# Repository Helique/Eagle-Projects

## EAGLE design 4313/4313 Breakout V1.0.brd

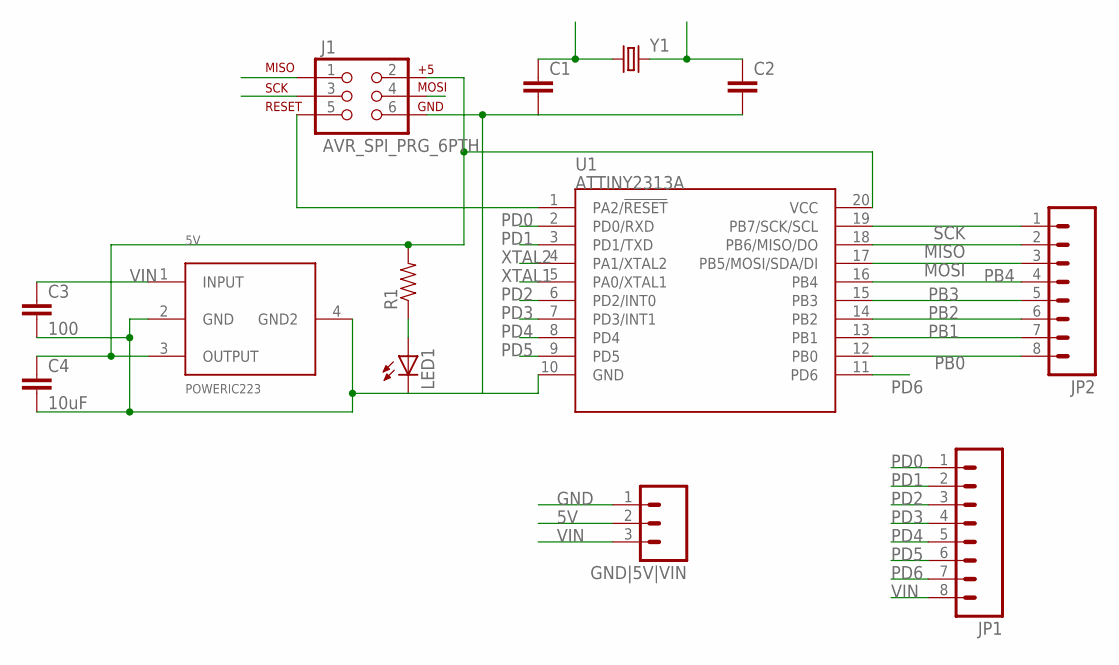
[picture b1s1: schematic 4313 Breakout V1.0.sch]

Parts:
5V: POWERIC223; SOT223
C1, C2: CAP1206; 1206
C3: 100; 1210
C4: 10uF; 1210
GND|5V|VIN: M03PTH; 1X03
J1: AVR_SPI_PRG_6PTH; 2X3
JP1, JP2: M081X08; 1X08
LED1: LED1206; LED-1206
R1: RESISTOR1206; 1206
U1: ATTINY2313A; SOP20W
Y1: CRYSTALHC49US; HC49US

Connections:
5V: 5V.3 (OUTPUT), C4.1, GND|5V|VIN.2, J1.2, R1.2, U1.20 (VCC)
GND: 5V.2 (GND), 5V.4 (GND2), C1.2, C2.2, C3.2, C4.2, GND|5V|VIN.1, J1.6, LED1.C, U1.10 (GND)
MISO: J1.1, JP2.2, U1.18 (PB6/MISO/DO)
MOSI: J1.4, JP2.3, U1.17 (PB5/MOSI/SDA/DI)
unnamed: LED1.A, R1.1
unnamed: J1.5, U1.1 (PA2/!RESET)
PB0: JP2.8, U1.12 (PB0)
PB1: JP2.7, U1.13 (PB1)
PB2: JP2.6, U1.14 (PB2)
PB3: JP2.5, U1.15 (PB3)
PB4: JP2.4, U1.16 (PB4)
PD0: JP1.1, U1.2 (PD0/RXD)
PD1: JP1.2, U1.3 (PD1/TXD)
PD2: JP1.3, U1.6 (PD2/INT0)
PD3: JP1.4, U1.7 (PD3/INT1)
PD4: JP1.5, U1.8 (PD4)
PD5: JP1.6, U1.9 (PD5)
PD6: JP1.7, U1.11 (PD6)
SCK: J1.3, JP2.1, U1.19 (PB7/SCK/SCL)
VIN: 5V.1 (INPUT), C3.1, GND|5V|VIN.3, JP1.8
XTAL1: C1.1, U1.5 (PA0/XTAL1), Y1.1
XTAL2: C2.1, U1.4 (PA1/XTAL2), Y1.2

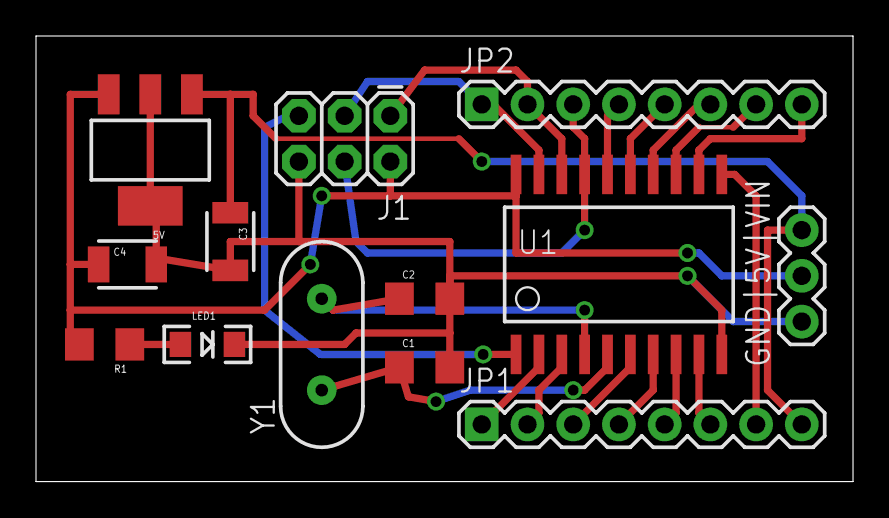
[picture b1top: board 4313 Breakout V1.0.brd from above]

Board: 2 copper layers, 45.4 x 24.8 mm, 13 parts (0 on the bottom side), 22 nets.

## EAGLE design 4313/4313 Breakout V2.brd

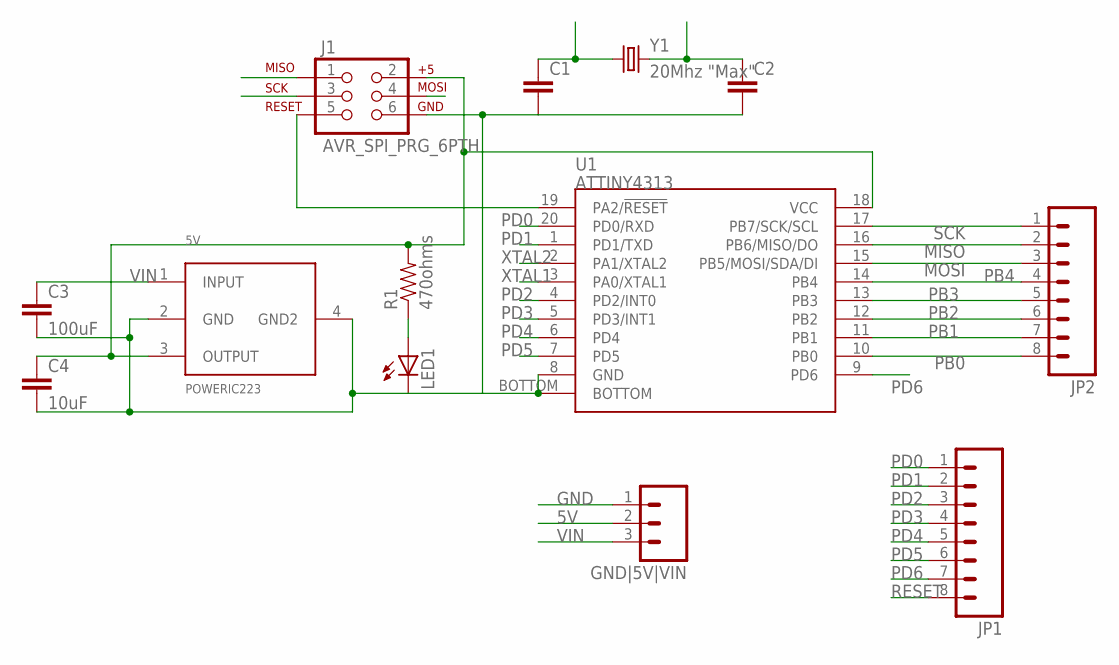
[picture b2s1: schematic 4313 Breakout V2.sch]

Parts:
5V: POWERIC223; SOT223
C1, C2: CAP1206; 1206
C3: 100uF; 1210
C4: 10uF; 1210
GND|5V|VIN: M03PTH; 1X03
J1: AVR_SPI_PRG_6PTH; 2X3
JP1, JP2: M081X08; 1X08
LED1: LED1206; LED-1206
R1: 470ohms; 1206
U1: ATTINY4313; MLF-20
Y1: 20Mhz "Max"; CRYSTAL-SMD-5X3

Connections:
5V: 5V.3 (OUTPUT), C4.1, GND|5V|VIN.2, J1.2, R1.2, U1.18 (VCC)
GND: 5V.2 (GND), 5V.4 (GND2), C1.2, C2.2, C3.2, C4.2, GND|5V|VIN.1, J1.6, LED1.C, U1.8 (GND), U1.BOTTOM
MISO: J1.1, JP2.2, U1.16 (PB6/MISO/DO)
MOSI: J1.4, JP2.3, U1.15 (PB5/MOSI/SDA/DI)
unnamed: LED1.A, R1.1
PB0: JP2.8, U1.10 (PB0)
PB1: JP2.7, U1.11 (PB1)
PB2: JP2.6, U1.12 (PB2)
PB3: JP2.5, U1.13 (PB3)
PB4: JP2.4, U1.14 (PB4)
PD0: JP1.1, U1.20 (PD0/RXD)
PD1: JP1.2, U1.1 (PD1/TXD)
PD2: JP1.3, U1.4 (PD2/INT0)
PD3: JP1.4, U1.5 (PD3/INT1)
PD4: JP1.5, U1.6 (PD4)
PD5: JP1.6, U1.7 (PD5)
PD6: JP1.7, U1.9 (PD6)
RESET: J1.5, JP1.8, U1.19 (PA2/!RESET)
SCK: J1.3, JP2.1, U1.17 (PB7/SCK/SCL)
VIN: 5V.1 (INPUT), C3.1, GND|5V|VIN.3
XTAL1: C1.1, U1.3 (PA0/XTAL1), Y1.1
XTAL2: C2.1, U1.2 (PA1/XTAL2), Y1.3 (2)

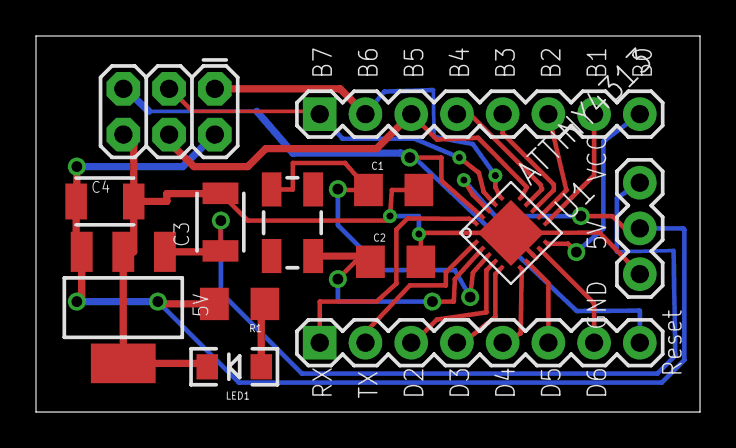
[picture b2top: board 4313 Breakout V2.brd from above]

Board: 2 copper layers, 36.9 x 20.9 mm, 13 parts (0 on the bottom side), 22 nets.

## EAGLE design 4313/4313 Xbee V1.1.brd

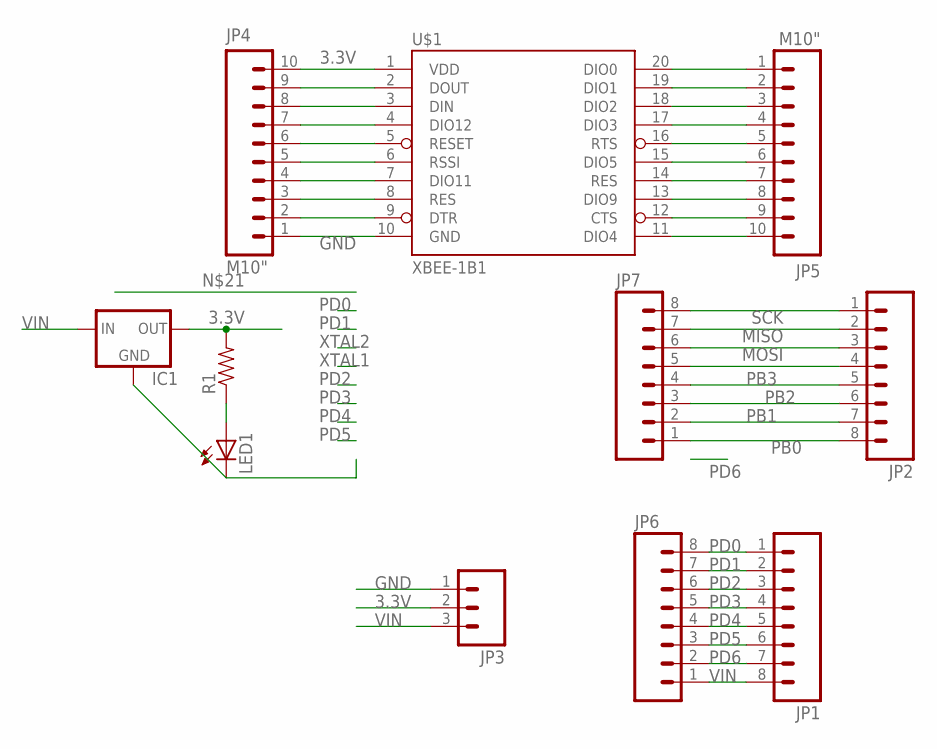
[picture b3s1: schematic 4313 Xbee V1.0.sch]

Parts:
IC1: V_REG_78XXSIDE; 78XXL
JP1, JP2, JP6, JP7: M081X08; 1X08
JP3: M03PTH; 1X03
JP4, JP5: M10"; 1X10
LED1: LED1206; LED-1206
R1: RESISTOR1206; 1206
U$1: XBEE-1B1; XBEE-1

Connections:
3.3V: IC1.OUT, JP3.2, JP4.10, R1.2, U$1.1 (VDD)
GND: IC1.GND, JP3.1, JP4.1, LED1.C, U$1.10 (GND)
MISO: JP2.2, JP7.7
MOSI: JP2.3, JP7.6
unnamed: LED1.A, R1.1
unnamed: JP4.2, U$1.9 (DTR)
unnamed: JP4.3, U$1.8 (RES)
unnamed: JP4.4, U$1.7 (DIO11)
unnamed: JP4.5, U$1.6 (RSSI)
unnamed: JP4.6, U$1.5 (RESET)
unnamed: JP4.7, U$1.4 (DIO12)
unnamed: JP4.8, U$1.3 (DIN)
unnamed: JP4.9, U$1.2 (DOUT)
unnamed: JP5.1, U$1.20 (DIO0)
unnamed: JP5.2, U$1.19 (DIO1)
unnamed: JP5.3, U$1.18 (DIO2)
unnamed: JP5.4, U$1.17 (DIO3)
unnamed: JP5.5, U$1.16 (RTS)
unnamed: JP5.6, U$1.15 (DIO5)
unnamed: JP5.7, U$1.14 (RES)
unnamed: JP5.8, U$1.13 (DIO9)
unnamed: JP5.9, U$1.12 (CTS)
unnamed: JP5.10, U$1.11 (DIO4)
PB0: JP2.8, JP7.1
PB1: JP2.7, JP7.2
PB2: JP2.6, JP7.3
PB3: JP2.5, JP7.4
PB4: JP2.4, JP7.5
PD0: JP1.1, JP6.8
PD1: JP1.2, JP6.7
PD2: JP1.3, JP6.6
PD3: JP1.4, JP6.5
PD4: JP1.5, JP6.4
PD5: JP1.6, JP6.3
PD6: JP1.7, JP6.2
SCK: JP2.1, JP7.8
VIN: IC1.IN, JP1.8, JP3.3, JP6.1

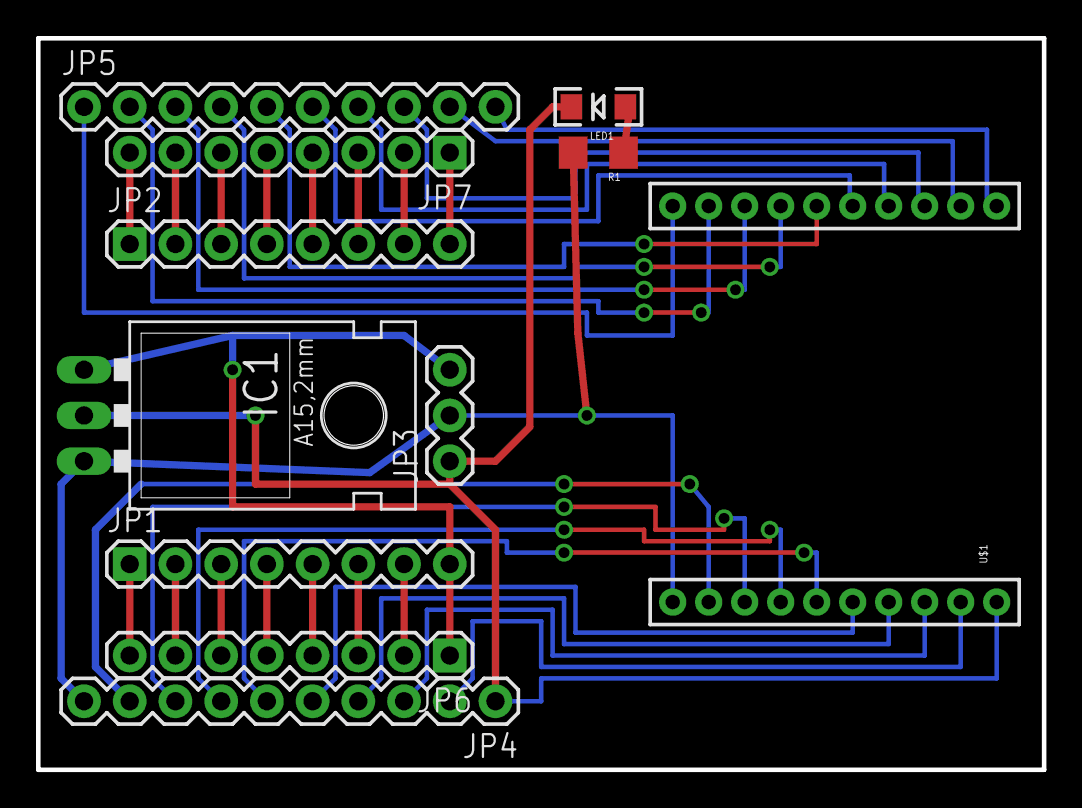
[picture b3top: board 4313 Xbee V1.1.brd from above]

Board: 2 copper layers, 55.9 x 40.6 mm, 11 parts (0 on the bottom side), 37 nets.

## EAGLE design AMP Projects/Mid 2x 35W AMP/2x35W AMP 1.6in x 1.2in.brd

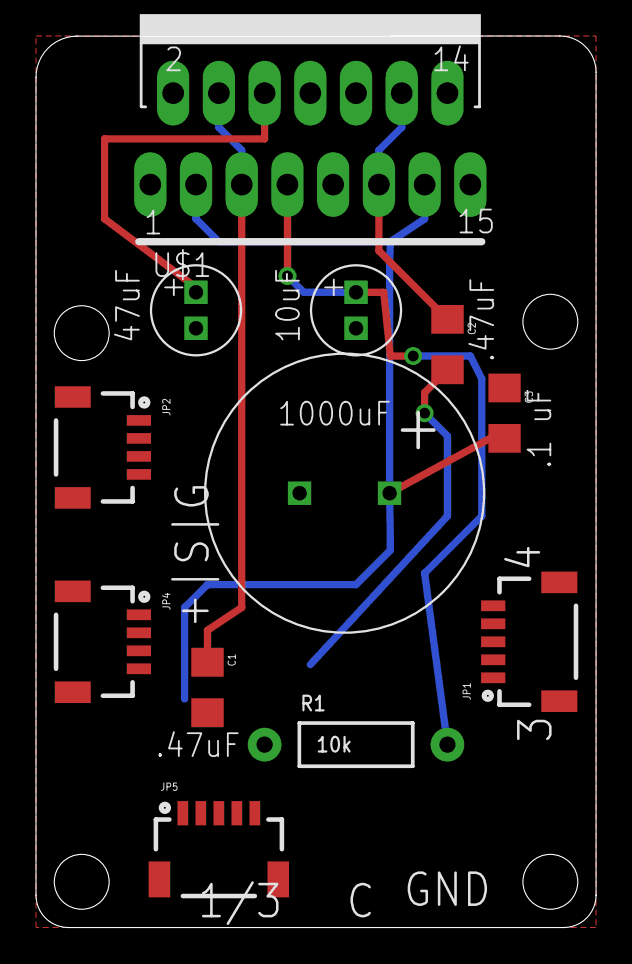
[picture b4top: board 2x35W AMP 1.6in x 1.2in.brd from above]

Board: 2 copper layers, 31.1 x 49.5 mm, 16 parts (0 on the bottom side), 15 nets.

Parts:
10UF, 47UF: 5MM-12.5MM-POLAR2MMX5MM; 2MMLEAD_5MMDIAMETER
1000UF: 5MM-12.5MM-POLAR5MMX12.5MM; 5MMLEAD_12.5MMDIAMETER
C1, C2: .47uF; 1206
C3: .1uF; 1206
JP1, JP5: 1X05-1MM-RA
JP2, JP4: 1X04-1MM-RA
R1: 10k; AXIAL-0.4
U$1: TDA7375V; MULTIWATT-15
U$2, U$3, U$4, U$5: STAND-OFF-TIGHT

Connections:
+5V: JP1.2, JP4.4, JP5.2
CLIP: JP1.5, U$1.10
GND: 10UF.-, 47UF.-, 1000UF.-, C3.1, JP1.1, JP4.1, JP4.3, JP5.1, U$1.8, U$1.9
IN1: C1.1, U$1.4, U$1.5
IN3: C2.1, U$1.11, U$1.12
unnamed: 10UF.+, R1.P$2, U$1.7
unnamed: 47UF.+, U$1.6
OUT1: JP2.4, U$1.1
OUT2: JP2.3, U$1.2
OUT3: JP2.2, U$1.15
OUT4: JP2.1, U$1.14
RAW_IN1: C1.2, JP1.4, JP5.4
RAW_IN3: C2.2, JP1.3, JP5.3
ST-BY: JP5.5, R1.P$1
VCC: 1000UF.+, C3.2, JP4.2, U$1.3, U$1.13

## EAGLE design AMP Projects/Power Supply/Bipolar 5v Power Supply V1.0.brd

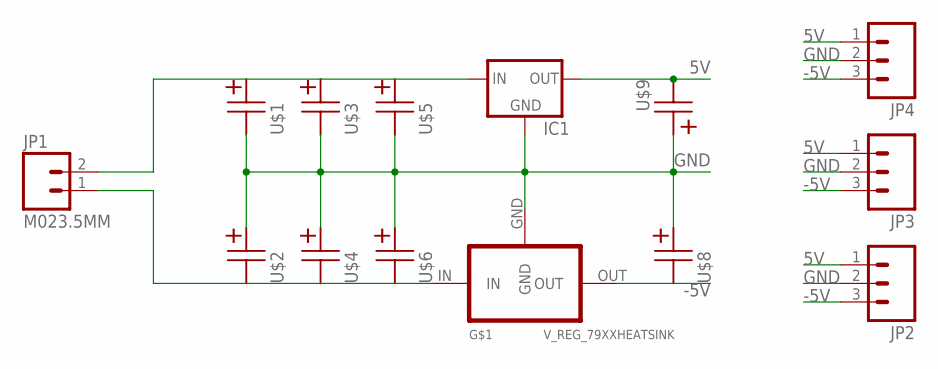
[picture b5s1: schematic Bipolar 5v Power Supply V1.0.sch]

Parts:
IC1: V_REG_78XXSINK; TO220-IGO
JP1: M023.5MM; SCREWTERMINAL-3.5MM-2
JP2, JP3, JP4: M03SCREW; SCREWTERMINAL-3.5MM-3
U$1, U$2, U$3, U$4, U$5, U$6: 5MM-12.5MM-POLAR5MMX12.5MM; 5MMLEAD_12.5MMDIAMETER
U$7: V_REG_79XXHEATSINK; TO220-IGO
U$8, U$9: 5MM-12.5MM-POLAR2MMX5MM; 2MMLEAD_5MMDIAMETER

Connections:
5V: IC1.OUT, JP2.1, JP3.1, JP4.1, U$9.+ (-)
-5V: JP2.3, JP3.3, JP4.3, U$7.OUT, U$8.+ (-)
GND: IC1.GND, JP2.2, JP3.2, JP4.2, U$1.+ (-), U$2.- (+), U$3.+ (-), U$4.- (+), U$5.+ (-), U$6.- (+), U$7.GND, U$8.- (+), U$9.- (+)
RAW+: IC1.IN, JP1.2, U$1.- (+), U$3.- (+), U$5.- (+)
RAW-: JP1.1, U$2.+ (-), U$4.+ (-), U$6.+ (-), U$7.IN

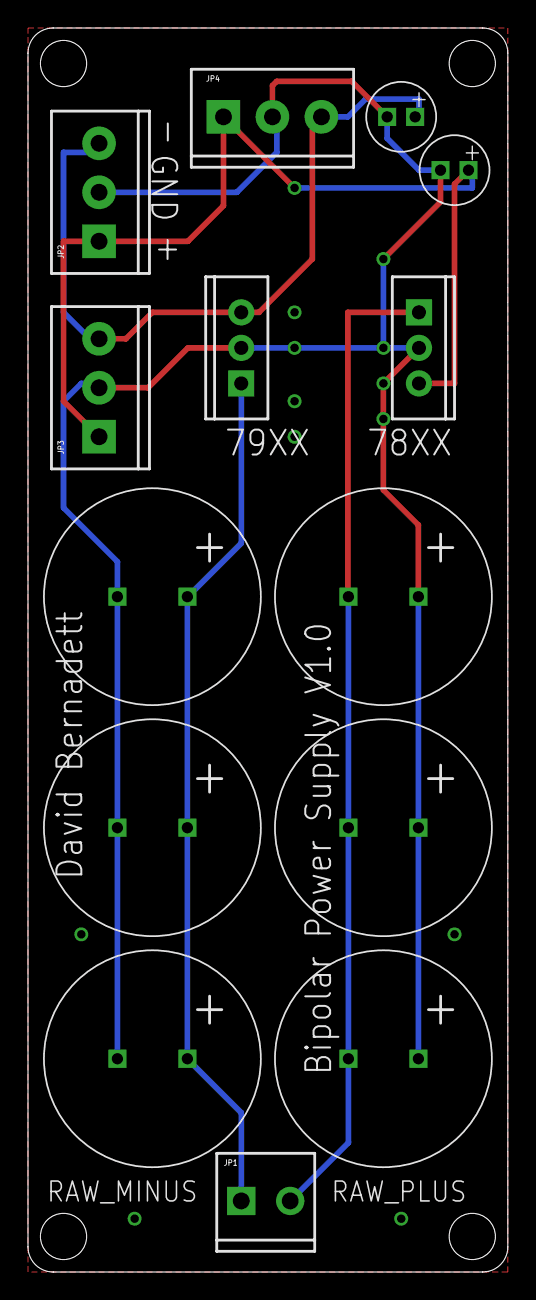
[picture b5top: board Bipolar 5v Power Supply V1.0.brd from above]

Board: 2 copper layers, 34.3 x 88.9 mm, 18 parts (0 on the bottom side), 5 nets.

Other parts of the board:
U$10, U$11, U$12, U$13: STAND-OFF

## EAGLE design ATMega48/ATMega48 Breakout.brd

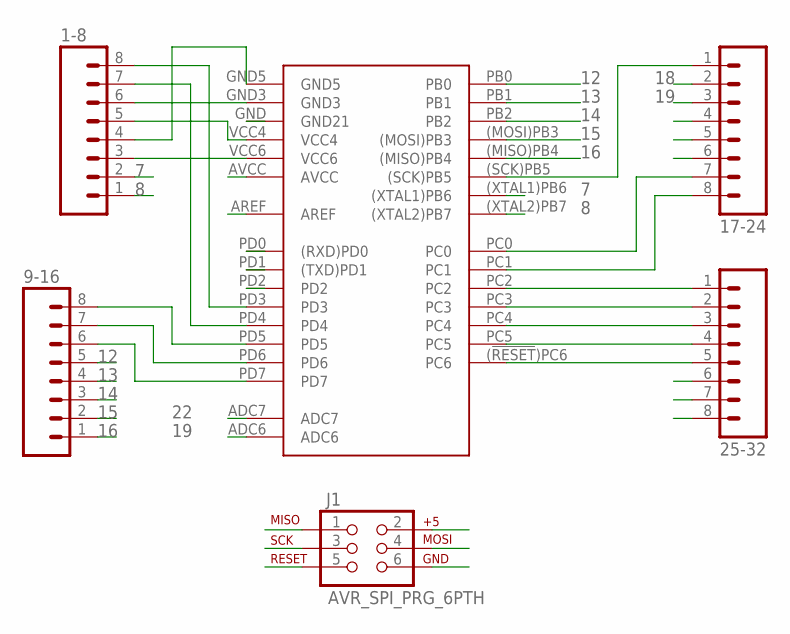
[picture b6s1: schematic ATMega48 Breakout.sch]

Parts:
1-8, 9-16, 17-24, 25-32: M081X08; 1X08
J1: AVR_SPI_PRG_6PTH; 2X3
MAIN: ATMEGA48; TQFP-32

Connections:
3: 1-8.6, J1.6, MAIN.GND3
4: 1-8.5, J1.2, MAIN.VCC4
7: 1-8.2, MAIN.(XTAL1)PB6
8: 1-8.1, MAIN.(XTAL2)PB7
12: 9-16.5, MAIN.PB0
13: 9-16.4, MAIN.PB1
14: 9-16.3, MAIN.PB2
15: 9-16.2, J1.4, MAIN.(MOSI)PB3
16: 9-16.1, J1.1, MAIN.(MISO)PB4
17: 17-24.1, J1.3, MAIN.(SCK)PB5
18: 17-24.2, MAIN.AVCC
19: 17-24.3, MAIN.ADC6
20: 17-24.4, MAIN.AREF
21: 17-24.5, MAIN.GND (GND21)
22: 17-24.6, MAIN.ADC7
29: 25-32.5, J1.5, MAIN.(!RESET!)PC6 (PC6)
30: 25-32.6, MAIN.PD0 ((RXD)PD0)
31: 25-32.7, MAIN.PD1 ((TXD)PD1)
32: 25-32.8, MAIN.PD2
unnamed: 1-8.8, MAIN.PD3
unnamed: 1-8.7, MAIN.PD4
unnamed: 1-8.4, MAIN.GND5
unnamed: 1-8.3, MAIN.VCC6
unnamed: 9-16.8, MAIN.PD5
unnamed: 9-16.7, MAIN.PD6
unnamed: 9-16.6, MAIN.PD7
unnamed: 17-24.7, MAIN.PC0
unnamed: 17-24.8, MAIN.PC1
unnamed: 25-32.1, MAIN.PC2
unnamed: 25-32.2, MAIN.PC3
unnamed: 25-32.3, MAIN.PC4
unnamed: 25-32.4, MAIN.PC5

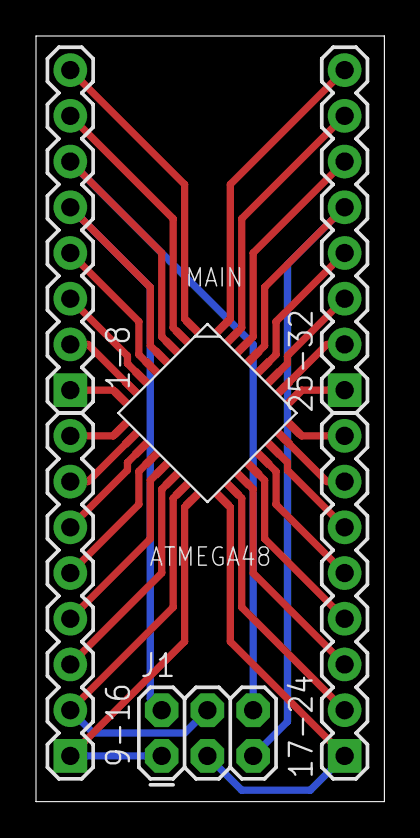
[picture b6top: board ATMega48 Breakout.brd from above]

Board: 2 copper layers, 19.4 x 42.5 mm, 6 parts (0 on the bottom side), 32 nets.

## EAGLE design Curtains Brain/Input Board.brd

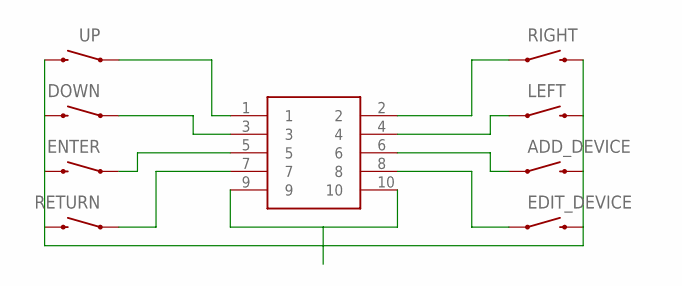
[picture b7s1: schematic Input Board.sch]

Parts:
ADD_DEVICE: SWITCH-MOMENTARY-212MM; TACTILE-PTH-12MM
DOWN: SWITCH-MOMENTARY-212MM; TACTILE-PTH-12MM
EDIT_DEVICE: SWITCH-MOMENTARY-212MM; TACTILE-PTH-12MM
ENTER: SWITCH-MOMENTARY-212MM; TACTILE-PTH-12MM
LEFT: SWITCH-MOMENTARY-212MM; TACTILE-PTH-12MM
RETURN: SWITCH-MOMENTARY-212MM; TACTILE-PTH-12MM
RIGHT: SWITCH-MOMENTARY-212MM; TACTILE-PTH-12MM
U$1: 10PIN_HEADER_MALE_SMD; 2X5-SHROUDED_SMD_BOTTOM
UP: SWITCH-MOMENTARY-212MM; TACTILE-PTH-12MM

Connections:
unnamed: U$1.1, UP.1
unnamed: DOWN.1, U$1.3
unnamed: ENTER.1, U$1.5
unnamed: RETURN.1, U$1.7
unnamed: RIGHT.1, U$1.2
unnamed: LEFT.1, U$1.4
unnamed: ADD_DEVICE.1, U$1.6
unnamed: EDIT_DEVICE.1, U$1.8
unnamed: ADD_DEVICE.3 (2), DOWN.3 (2), EDIT_DEVICE.3 (2), ENTER.3 (2), LEFT.3 (2), RETURN.3 (2), RIGHT.3 (2), U$1.9, U$1.10, UP.3 (2)

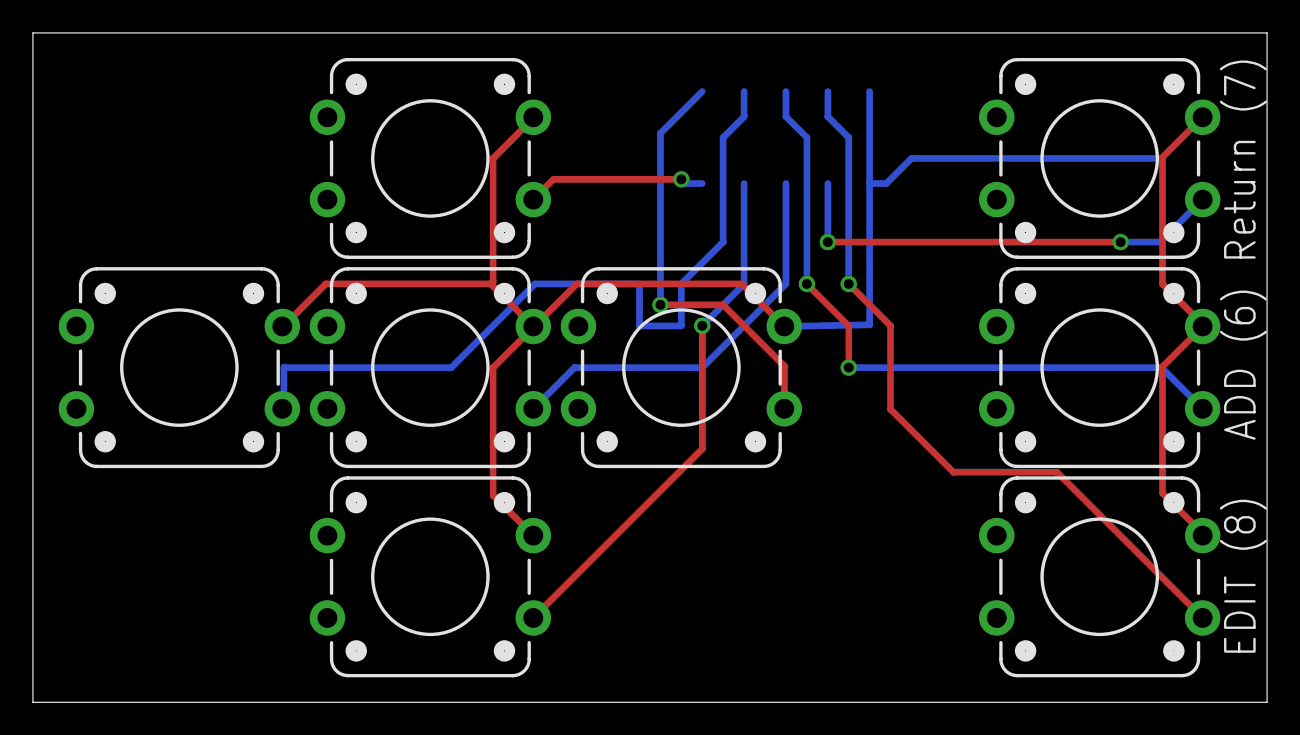
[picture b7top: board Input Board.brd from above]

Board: 2 copper layers, 74.9 x 40.6 mm, 9 parts (0 on the bottom side), 9 nets.

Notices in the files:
parts and their libraries:
SparkFun-DigitalIC: Licensing: CC v3.0 Share-Alike You are welcome to use this library for commercial purposes.
